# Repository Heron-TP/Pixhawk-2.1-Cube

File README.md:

# Pixhawk-2.1-Cube

This git repository contains a Carrier Board for the Pixhawk 2.1 Cube, using the open source EDA KiCad.
All hardware and coresponding EDA-files are subject to the CC-BY-SA 3.0 license.

All included or imported content is subject to its resprective licencing.

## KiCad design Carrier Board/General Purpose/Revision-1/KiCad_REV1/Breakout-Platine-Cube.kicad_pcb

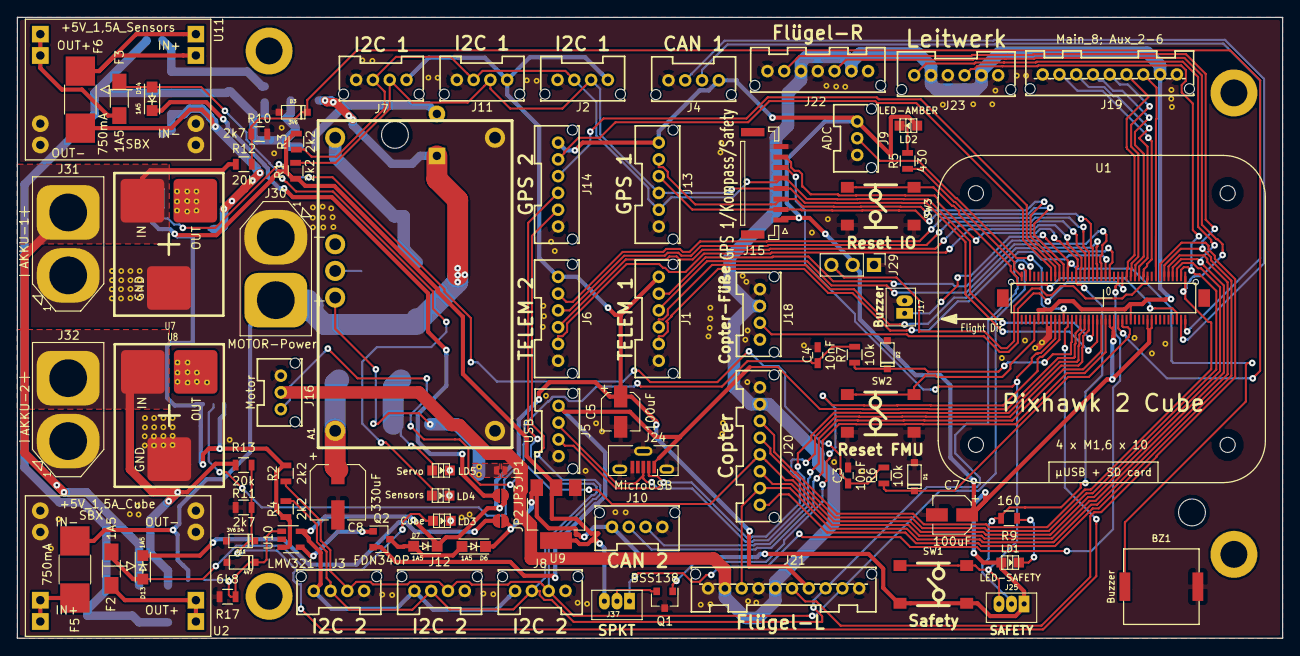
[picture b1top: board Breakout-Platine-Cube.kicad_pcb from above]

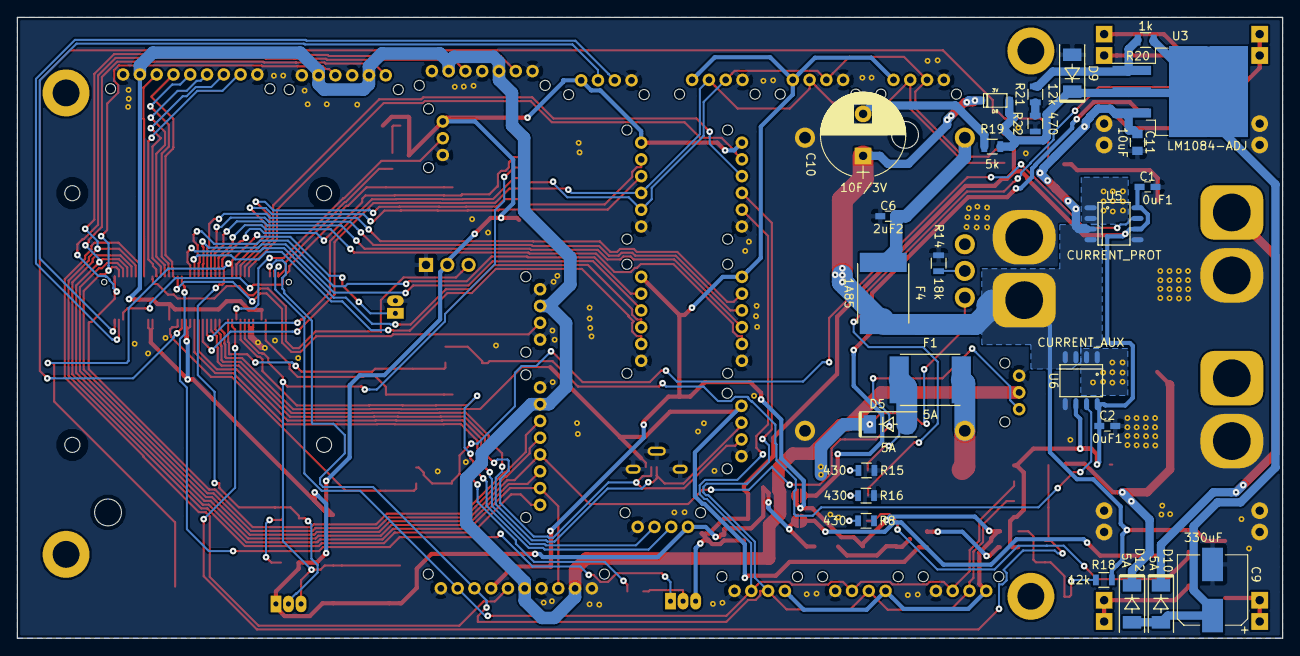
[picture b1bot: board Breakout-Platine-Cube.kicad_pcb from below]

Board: 2 copper layers, 150.8 x 74.0 mm, 108 parts (25 on the bottom side), 89 nets.

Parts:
A1: +5V_5A_Servo; TEXAS-R-PDSS-T7
BZ1: Buzzer; PKMCS0909E4000-R1
C1, C2: 0uF1; C_0603_HandSoldering
C3, C4: 10nF; C_0603_HandSoldering
C5, C7: 100uF; CP_Elec_4x5.8
C6: 2uF2; C_0603_HandSoldering
C8: 330uF; CP_Elec_6.3x5.8
C9: 330uF; CP_Elec_8x10.5
C10: 10F/3V; CP_Radial_D10.0mm_P5.00mm
C11: 10uF; C_0805
D1, D2, D3, D4: 3V6; sod123
D5, D10, D12: 5A; SOD-128
D6, D7, D13, D14: 1A5; SOD-123F
D8: 3V; sod123
D9: 30V/2W; SOD-128
D11: 4V7; sod123
F1: 5A; Fuse_SMD2920
F2, F3: 1A5; R_1206_HandSoldering
F4: 1A85; Fuse_SMD2920
F5, F6: 750mA; R_1812_HandSoldering
J1: TELEM 1; JST-PA-06_Top-entry-type
J2, J7, J11: I2C 1; JST-PA-04_Top-entry-type
J3, J8, J12: I2C 2; JST-PA-04_Top-entry-type
J4: CAN 1; JST-PA-04_Top-entry-type
J5: USB; JST-PA-04_Top-entry-type
J6: TELEM 2; JST-PA-06_Top-entry-type
J9: ADC; JST-PA-03_Top-entry-type
J10: CAN 2; JST-PA-04_Top-entry-type
J13: GPS 1; JST-PA-06_Top-entry-type
J14: GPS 2; JST-PA-06_Top-entry-type
J15: GPS 1/Kompass/Safety; JST_GH_BM08B-GHS-TBT_08x1.25mm_Straight
J16: Motor; JST-PA-03_Top-entry-type
J17: Buzzer; JST_ZH_B2B-ZR
J18: Copter-Füße; JST-PA-04_Top-entry-type
J19: Main_8; Aux_2-6; JST-PA-09_Top-entry-type
J20: Copter; JST-PA-08_Top-entry-type
J21: Flügel-L; JST-PA-10_Top-entry-type
J22: Flügel-R; JST-PA-07_Top-entry-type
J23: Leitwerk; JST-PA-06_Top-entry-type
J24: MicroUSB; USB_Micro-B_Vertical_Molex-105133-0001
J25: SAFETY; JST_ZH_B3B-ZR
J29: RC IN; Pin_Header_Straight_1x03_Pitch2.54mm
J30: MOTOR-Power; XT60-Top_Entry
J31: AKKU-1; XT60-Top_Entry
J32: AKKU-2; XT60-Top_Entry
J37: SPKT; JST_ZH_B3B-ZR
JP1: Servo; JUMPER-SOLDER-SMD_mit_flaechenanschluss
JP2: Cube; JUMPER-SOLDER-SMD
JP3: Sensors; JUMPER-SOLDER-SMD
LD1: LED-SAFETY; Led_0805
LD2: LED-AMBER; Led_0805
LD3: Cube; Led_0805
LD4: Sensors; Led_0805
LD5: Servo; Led_0805
Q1: BSS138; SOT-23
Q2: FDN340P; SOT-23
R1, R2, R3, R4: 2k2; R_0805
R5, R8, R15, R16: 430; R_0805
R6, R7: 10k; R_0805
R9: 160; R_0805
R10, R11: 2k7; R_0805
R12, R13: 20k; R_0805
R14: 18k; R_0805
R17: 6k8; R_0805
R18, R21: 12k; R_0805
R19: 5k; R_0805
R20: 1k; R_0805
R22: 470; R_0805
SW1: Safety; CK-PTS645-SMD
SW2: Reset FMU; CK-PTS645-SMD
SW3: Reset IO; CK-PTS645-SMD
U1: Pixhawk_2_Cube_80-Pin_Header; Pixhawk-2_Cube
U2: +5V_1,5A_Cube; Mini_MP1584EN
U3: LM1084-ADJ; TO-263-3_TabPin2
U5: CURRENT_PROT; SO-8
U6: CURRENT_AUX; SO-8
U7: Ideal_Diode_PROT; Ideale_Diode_Gen-I
U8: Ideal_Diode_AUX; Ideale_Diode_Gen-I
U9: LD1117S33TR_SOT223; SOT-223-3Lead_TabPin2
U10: LMV321; SOT-23-5
U11: +5V_1,5A_Sensors; Mini_MP1584EN

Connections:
+3V3: C1.1, C2.1, J37.3, R1.1, R2.1, R3.1, R4.1, U5.6, U5.8, U6.6, U6.8, U9.2, U10.3
+5V_Cube: C7.1, D6.2, J4.1, J9.1, J10.1, J13.1, J14.1, J15.1, J25.1, J29.2, JP2.1, LD1.1, LD2.1, SW1.1, SW1.2, U1.43, U1.45, U1.61, U1.63, U9.3
+5V_Sensors: C5.1, D7.2, J1.1, J2.1, J3.1, J6.1, J7.1, J8.1, J11.1, J12.1, J21.7, JP3.1, U10.5
+5V_Servo: J16.2, J18.2, J19.2, J20.2, J21.2, J21.5, J22.2, J22.5, J23.2, J23.5, JP1.1, U1.9, U1.53
/ALARM: BZ1.1, J17.1, U1.24
/AUX_BATT­_CURRENT_SENS: D2.2, R7.2, U1.25
/AUX_BATT­_CURRENT_SENS_1: C4.1, R7.1, U6.7
/AUX_BATT­_VOLTAGE_SENS: D4.2, R11.1, R13.2, U1.23
/BATT­_CURRENT_SENS_PROT: D1.2, R6.2, U1.49
/BATT­_CURRENT_SENS_PROT_1: C3.1, R6.1, U5.7
/BATT­_VOLTAGE_SENS_PROT: D3.2, R10.1, R12.2, U1.47
/CAN_H_1: J4.2, U1.79
/CAN_H_2: J10.2, U1.41
/CAN_L_1: J4.3, U1.77
/CAN_L_2: J10.3, U1.39
/FMU-CH1-PROT: J18.3, U1.50
/FMU-CH2-PROT: J19.4, U1.52
/FMU-CH3-PROT: J19.5, U1.54
/FMU-CH4-PROT: J19.6, U1.56
/FMU-CH5-PROT: J19.7, U1.58
/FMU-CH6-PROT: J19.8, U1.60
/FMU-~LED_AMBER: R5.1, U1.2
/FMU-~RESET: SW2.1, SW2.2, U1.7
/I2C_1_SCL: J2.2, J7.2, J11.2, J13.4, J15.4, R1.2, U1.37
/I2C_1_SDA: J2.3, J7.3, J11.3, J13.5, J15.5, R3.2, U1.35
/I2C_2_SCL: J3.2, J8.2, J12.2, J14.4, J21.8, R4.2, U1.6
/I2C_2_SDA: J3.3, J8.3, J12.3, J14.5, J21.9, R2.2, U1.4
/IO-CH1-PROT: J20.3, J22.3, U1.80
/IO-CH2-PROT: J20.4, J23.3, U1.78
/IO-CH3-PROT: J16.3, J20.5, U1.76
/IO-CH4-PROT: J20.6, J23.6, U1.74
/IO-CH5-PROT: J20.7, J21.3, U1.72
/IO-CH6-PROT: J20.8, J22.6, U1.70
/IO-CH7-PROT: J21.6, U1.68
/IO-CH8-PROT: J19.3, U1.66
/IO-USART1_RX_SPECTRUM_DSM: J37.1, U1.48
/IO-~LED_SAFETY_PROT: J15.7, J25.2, R9.2, U1.28
/IO-~RESET: SW3.1, SW3.2, U1.75
/OTG_DM1: J5.3, J24.2, U1.33
/OTG_DP1: J5.2, J24.3, U1.31
/PPM_SBUS_PROT: J29.3, U1.62
/PREASSURE_SENS_IN: J9.2, U1.21
/Power_Supply/Power_Supply: C10.1, C11.1, D8.2, F4.1, F5.1, F6.1, J30.1, R18.1, U3.3, U5.3, U5.4, U6.3, U6.4
/Power_Supply/Recuperate: C9.1, D8.1, D9.2, D10.1, D12.1, R19.2, R20.1, U3.2
/SAFETY: J15.6, J25.3, SW1.3, SW1.4, U1.17
/SERIAL1_CTS: J1.4, U1.44
/SERIAL1_RTS: J1.5, U1.42
/SERIAL1_RX: J1.3, U1.38
/SERIAL1_TX: J1.2, U1.40
/SERIAL2_CTS: J6.4, U1.32
/SERIAL2_RTS: J6.5, U1.30
/SERIAL2_RX: J6.3, U1.34
/SERIAL2_TX: J6.2, U1.36
/SERIAL_3_RX: J13.2, J15.3, U1.20
/SERIAL_3_TX: J13.3, J15.2, U1.22
/SERIAL_4_RX: J14.2, U1.16
/SERIAL_4_TX: J14.3, U1.18
/VBUS: J5.1, J24.1, Q2.2, U1.29
/VDD_3V3_SPECTRUM_EN: Q1.1, U1.19
GND: A1.1, A1.7, BZ1.2, C1.2, C2.2, C3.2, C4.2, C5.2, C6.1, C7.2, C8.2, C9.2, C11.2, D1.1, D2.1, D3.1, D4.1, D9.1, D11.1, J1.6, J2.4, J3.4, J4.4, J5.4, J6.6, J7.4, J8.4, J9.3, J10.4, J11.4, J12.4, J13.6, J14.6, J15.8, J16.1, J17.2, J18.1, J18.4, J19.1, J19.9, J20.1, J21.1, J21.4, J21.10, J22.1, J22.4, J22.7, J23.1, J23.4, J24.5, J24.6, J29.1, J30.2, J31.2, J32.2, Q1.3, R8.1, R10.2, R11.2, R14.1, R15.1, R16.1, R17.2, R22.1, SW2.3, SW2.4, SW3.3, SW3.4, U1.13, U1.15, U2.3, U2.4, U2.5, U2.6, U5.5, U6.5, U7.3, U8.3, U9.1, U10.2, U11.3, U11.4, U11.5, U11.6
unnamed: A1.2, C6.2, F4.2
unnamed: A1.4, R14.2
unnamed: A1.5, D5.2, JP1.2
unnamed: A1.6, C8.1, F1.1
unnamed: C10.2, R19.1
unnamed: D5.1, F1.2, LD5.1
unnamed: D6.1, D7.1, Q2.3
unnamed: D10.2, J31.1, R12.1, U7.1
unnamed: D11.2, R17.1, R18.2, U10.1
unnamed: D12.2, J32.1, R13.1, U8.1
unnamed: D13.1, F2.2, LD3.1
unnamed: D13.2, JP2.2
unnamed: D14.1, F3.2, LD4.1
unnamed: D14.2, JP3.2
unnamed: F2.1, U2.7, U2.8
unnamed: F3.1, U11.7, U11.8
unnamed: F5.2, U2.1, U2.2
unnamed: F6.2, U11.1, U11.2
unnamed: J37.2, Q1.2
unnamed: LD1.2, R9.1
unnamed: LD2.2, R5.2
unnamed: LD3.2, R8.2
unnamed: LD4.2, R16.2
unnamed: LD5.2, R15.2
unnamed: Q2.1, U10.4
unnamed: R20.2, R21.2, U3.1
unnamed: R21.1, R22.2
unnamed: U5.1, U5.2, U7.2
unnamed: U6.1, U6.2, U8.2

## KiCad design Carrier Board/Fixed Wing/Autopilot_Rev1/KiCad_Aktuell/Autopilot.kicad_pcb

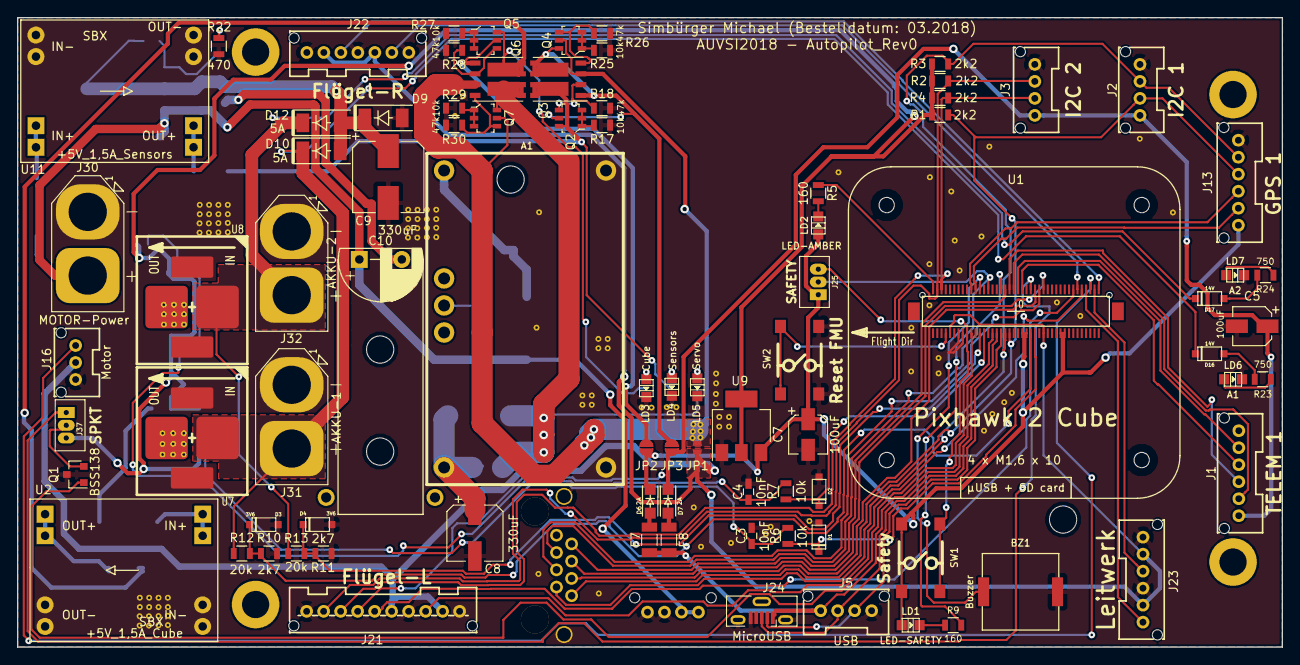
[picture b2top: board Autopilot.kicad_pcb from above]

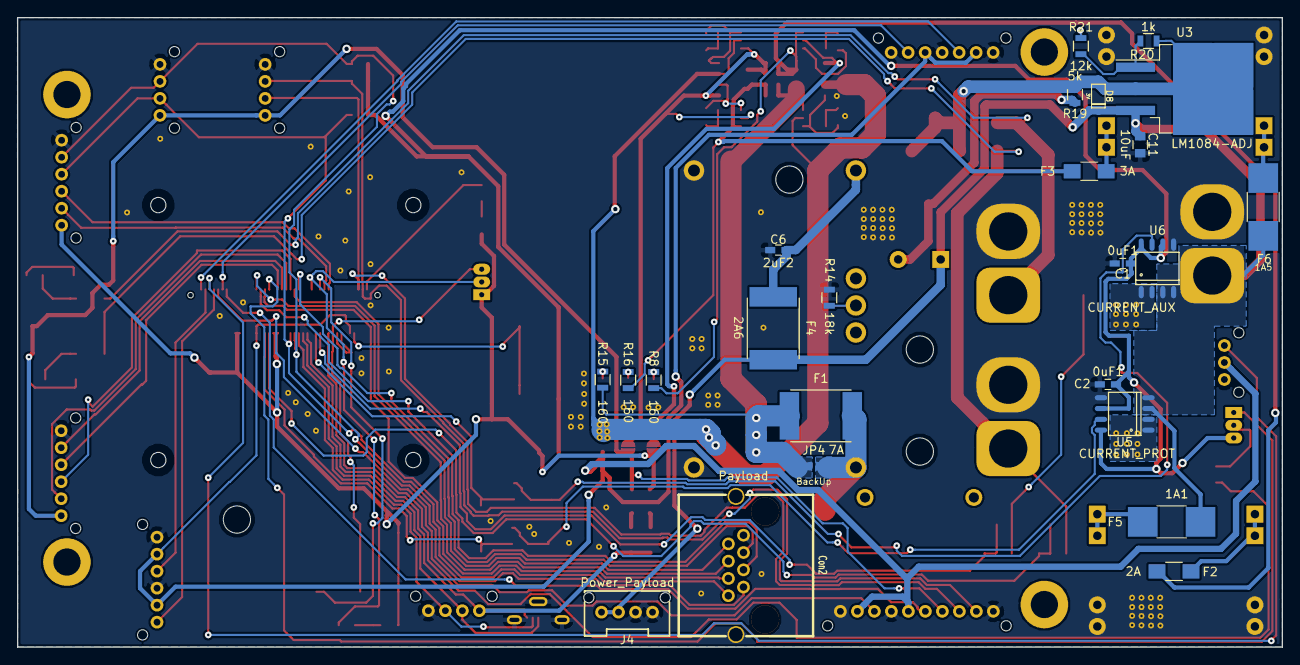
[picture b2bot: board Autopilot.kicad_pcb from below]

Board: 2 copper layers, 148.8 x 74.1 mm, 109 parts (24 on the bottom side), 85 nets.

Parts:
A1: +5V3_6A_Servo; TEXAS-R-PDSS-T7
BZ1: Buzzer; PKMCS0909E4000-R1
C1, C2: 0uF1; C_0603_HandSoldering
C3, C4: 10nF; C_0603_HandSoldering
C5, C7: 100uF; CP_Elec_4x5.8
C6: 2uF2; C_0603_HandSoldering
C8: 330uF; CP_Elec_6.3x5.8
C9: 330uF; CP_Elec_8x10.5
C10: 10F/3V; CP_Radial_D10.0mm_P5.00mm_horizontal
C11: 10uF; C_0805
Con2: Payload; RJHSE-5380
D1, D2, D3, D4: 3V6; sod123
D6, D7: 2A; SOD-123F
D8: 3V; sod123
D9: 30V/2W; SOD-128
D10, D12: 5A; SOD-128
D16, D17: 14V; sod123
F1: 7A; Fuse_SMD2920
F2: 2A; R_1206_HandSoldering
F3: 3A; R_1206_HandSoldering
F4: 2A6; Fuse_SMD2920
F5: 1A1; R_1812_HandSoldering
F6: 1A5; R_1812_HandSoldering
F7, F8: 1A5; R_1206_3216Metric
J1: TELEM 1; JST-PA-06_Top-entry-type
J2: I2C 1; JST-PA-04_Top-entry-type
J3: I2C 2; JST-PA-04_Top-entry-type
J4: Power_Payload; JST-PA-04_Top-entry-type
J5: USB; JST-PA-04_Top-entry-type
J13: GPS 1; JST-PA-06_Top-entry-type
J16: Motor; JST-PA-03_Top-entry-type
J21: Flügel-L; JST-PA-10_Top-entry-type
J22: Flügel-R; JST-PA-07_Top-entry-type
J23: Leitwerk; JST-PA-06_Top-entry-type
J24: MicroUSB; USB_Micro-B_Vertical_Molex-105133-0001
J25: SAFETY; JST_ZH_B3B-ZR
J30: MOTOR-Power; XT60-Top_Entry
J31: AKKU-1; XT60-Top_Entry
J32: AKKU-2; XT60-Top_Entry
J37: SPKT; JST_ZH_B3B-ZR
JP1: Servo; JUMPER-SOLDER-SMD_mit_flaechenanschluss
JP2: Cube; JUMPER-SOLDER-SMD
JP3: Sensors; JUMPER-SOLDER-SMD
JP4: BackUp; JUMPER-SOLDER-SMD_mit_flaechenanschluss
LD1: LED-SAFETY; Led_0805
LD2: LED-AMBER; Led_0805
LD3: Cube; Led_0805
LD4: Sensors; Led_0805
LD5: Servo; Led_0805
LD6: A1; Led_0805
LD7: A2; Led_0805
Q1: BSS138; SOT-23
Q2, Q4, Q5, Q7: DMMT5401-7-F; SOT-23-6
Q3, Q6: SI7997DP; PowerPAK_SO-8_Dual
R1, R2, R3, R4: 2k2; R_0805
R5, R8, R9, R15, R16: 160; R_0805
R6, R7, R17, R25, R27, R29: 10k; R_0805
R10, R11: 2k7; R_0805
R12, R13: 20k; R_0805
R14: 18k; R_0805
R18, R26, R28, R30: 47k; R_0805
R19: 5k; R_0805
R20: 1k; R_0805
R21: 12k; R_0805
R22: 470; R_0805
R23, R24: 750; R_0805
SW1: Safety; CK-PTS645-SMD
SW2: Reset FMU; CK-PTS645-SMD
U1: Pixhawk_2_Cube_80-Pin_Header; Pixhawk-2_Cube
U2: +5V_1,5A_Cube; Mini_MP1584EN
U3: LM1084-ADJ; TO-263-3_TabPin2
U5: CURRENT_PROT; SO-8
U6: CURRENT_AUX; SO-8
U7: Ideal_Diode_PROT; Ideale_Diode_Gen-II_rev00
U8: Ideal_Diode_AUX; Ideale_Diode_Gen-II_rev00
U9: LD1117S33TR_SOT223; SOT-223-3Lead_TabPin2
U11: +5V_1,5A_Sensors; Mini_MP1584EN

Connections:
+3V3: C1.1, C2.1, J37.3, R1.1, R2.1, R3.1, R4.1, U5.6, U5.8, U6.6, U6.8, U9.2
+5V_Cube: C7.1, D6.2, J13.1, J25.1, JP2.1, LD1.1, LD2.1, SW1.1, SW1.2, U1.43, U1.45, U1.61, U1.63, U9.3
+5V_Sensors: C5.1, D7.2, J1.1, J2.1, J3.1, J21.7, JP3.1
+5V_Servo: J16.2, J21.2, J21.5, J22.2, J22.5, J23.2, J23.5, JP1.1, U1.9, U1.53
/ALARM: BZ1.1, U1.24
/AUX_BATT­_CURRENT_SENS: D2.2, R7.2, U1.25
/AUX_BATT­_CURRENT_SENS_1: C4.1, R7.1, U6.7
/AUX_BATT­_VOLTAGE_SENS: D4.2, R11.1, R13.2, U1.23
/BATT­_CURRENT_SENS_PROT: D1.2, R6.2, U1.49
/BATT­_CURRENT_SENS_PROT_1: C3.1, R6.1, U5.7
/BATT­_VOLTAGE_SENS_PROT: D3.2, R10.1, R12.2, U1.47
/FMU-CH1-PROT: Con2.6, U1.50
/FMU-CH2-PROT: Con2.5, U1.52
/FMU-CH3-PROT: Con2.4, U1.54
/FMU-~LED_AMBER: R5.1, U1.2
/FMU-~RESET: SW2.1, SW2.2, U1.7
/I2C_1_SCL: Con2.8, J2.2, J13.4, R1.2, U1.37
/I2C_1_SDA: Con2.7, J2.3, J13.5, R3.2, U1.35
/I2C_2_SCL: J3.2, J21.8, R4.2, U1.6
/I2C_2_SDA: J3.3, J21.9, R2.2, U1.4
/IO-CH1-PROT: J22.3, U1.80
/IO-CH2-PROT: J23.3, U1.78
/IO-CH3-PROT: J16.3, U1.76
/IO-CH4-PROT: J23.6, U1.74
/IO-CH5-PROT: J21.3, U1.72
/IO-CH6-PROT: J22.6, U1.70
/IO-CH7-PROT: J21.6, U1.68
/IO-USART1_RX_SPECTRUM_DSM: J37.1, U1.48
/IO-~LED_SAFETY_PROT: J25.2, R9.2, U1.28
/OTG_DM1: J5.3, J24.2, U1.33
/OTG_DP1: J5.2, J24.3, U1.31
/Power_Supply: C10.1, C11.1, D8.2, F4.1, F5.1, F6.1, J4.1, J4.2, J30.1, U3.3, U5.3, U5.4, U6.3, U6.4
/Power_Supply/CrossFeed: JP1.2, Q3.3, Q4.5, Q6.3, Q7.5
/Power_Supply/ID_CrossFeed: JP3.2, Q2.5, Q3.1, Q3.6, Q4.6
/Power_Supply/ID_Cub_1: F2.2, Q5.6, Q6.5, R8.2
/Power_Supply/ID_Cub_2: JP2.2, Q5.5, Q6.1
/Power_Supply/ID_Sen_1: F3.2, Q2.6, Q3.5, R16.2
/Power_Supply/ID_Ser_1: F1.2, JP4.1, Q6.6, Q7.6, R15.2
/Power_Supply/Recuperate: C9.1, D8.1, D9.2, D10.1, D12.1, R19.2, R20.1, U3.2
/SAFETY: J25.3, SW1.3, SW1.4, U1.17
/SERIAL1_CTS: J1.4, U1.44
/SERIAL1_RTS: J1.5, U1.42
/SERIAL1_RX: J1.3, U1.38
/SERIAL1_TX: J1.2, U1.40
/SERIAL2_RX: Con2.3, U1.34
/SERIAL2_TX: Con2.2, U1.36
/SERIAL_3_RX: J13.3, U1.20
/SERIAL_3_TX: J13.2, U1.22
/VBUS: F7.1, F8.1, J5.1, J24.1, U1.29
/VDD_3V3_SPECTRUM_EN: Q1.1, U1.19
GND: A1.1, A1.7, BZ1.2, C1.2, C2.2, C3.2, C4.2, C5.2, C6.1, C7.2, C8.2, C9.2, C11.2, Con2.1, Con2.9, D1.1, D2.1, D3.1, D4.1, D9.1, J1.6, J2.4, J3.4, J4.3, J4.4, J5.4, J13.6, J16.1, J21.1, J21.4, J21.10, J22.1, J22.4, J22.7, J23.1, J23.4, J24.5, J24.6, J30.2, J31.2, J32.2, LD3.2, LD4.2, LD5.2, LD6.2, LD7.2, Q1.3, R10.2, R11.2, R14.1, R17.1, R18.1, R22.1, R25.1, R26.1, R27.1, R28.1, R29.1, R30.1, SW2.3, SW2.4, U1.13, U1.15, U2.3, U2.4, U2.5, U2.6, U5.5, U6.5, U7.3, U8.3, U9.1, U11.3, U11.4, U11.5, U11.6
unnamed: A1.2, C6.2, F4.2
unnamed: A1.4, R14.2
unnamed: A1.6, C8.1, F1.1, JP4.2
unnamed: C10.2, R19.1
unnamed: D6.1, F7.2
unnamed: D7.1, F8.2
unnamed: D10.2, D16.2, J31.1, R12.1, U7.1
unnamed: D12.2, D17.2, J32.1, R13.1, U8.1
unnamed: D16.1, R23.2
unnamed: D17.1, R24.2
unnamed: F2.1, U2.7, U2.8
unnamed: F3.1, U11.7, U11.8
unnamed: F5.2, U2.1, U2.2
unnamed: F6.2, U11.1, U11.2
unnamed: J37.2, Q1.2
unnamed: LD1.2, R9.1
unnamed: LD2.2, R5.2
unnamed: LD3.1, R8.1
unnamed: LD4.1, R16.1
unnamed: LD5.1, R15.1
unnamed: LD6.1, R23.1
unnamed: LD7.1, R24.1
unnamed: Q2.1, Q2.2, Q2.3, R17.2
unnamed: Q2.4, Q3.2, R18.2
unnamed: Q3.4, Q4.4, R26.2
unnamed: Q4.1, Q4.2, Q4.3, R25.2
unnamed: Q5.1, Q5.2, Q5.3, R27.2
unnamed: Q5.4, Q6.2, R28.2
unnamed: Q6.4, Q7.4, R30.2
unnamed: Q7.1, Q7.2, Q7.3, R29.2
unnamed: R20.2, R21.2, U3.1
unnamed: R21.1, R22.2
unnamed: U5.1, U5.2, U7.2
unnamed: U6.1, U6.2, U8.2

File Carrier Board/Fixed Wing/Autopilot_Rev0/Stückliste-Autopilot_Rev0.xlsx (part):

Reference | Value | Footprint | Count | Datasheet | FootprintLib | banggood# | digikey# | farnell# | manf# | vorhanden | #mouser | Manufacturer | mouser# | bangood# | BOM
U1 | Pixhawk_2_Cube_80-Pin_Header | Pixhawk-2_Cube | 1 |  | Pixhawk_2-Cube | Value | Value | 1874484 | DF17(1.0H)-80DP-0.5V(57) | Value
J2 | I2C 1 | JST-PA-04_Top-entry-type | 1 |  | JST_PA
R1;R3;R2;R4 | 2k2 | R_0805 | 4 |  | Resistors-Mini-SMD |  |  |  | vorhanden [0805]
J3 | I2C 2 | JST-PA-04_Top-entry-type | 1 |  | JST_PA
J1 | TELEM 1 | JST-PA-06_Top-entry-type | 1 |  | JST_PA
J13 | GPS 1 | JST-PA-06_Top-entry-type | 1 |  | JST_PA |  |  |  | B06B-PASK-1 [vorhanden]
J5 | USB | JST-PA-04_Top-entry-type | 1 |  | JST_PA
J23 | Leitwerk | JST-PA-06_Top-entry-type | 1 |  | JST_PA |  | Value |  | B06B-PASK-1(LF)(SN) | ja
J16 | Motor | JST-PA-03_Top-entry-type | 1 |  | JST_PA |  | 455-1833-ND |  | B03B-PASK-1(LF)(SN) | ja
J21 | Flügel-L | JST-PA-10_Top-entry-type | 1 |  | JST_PA |  | Value |  | B10B-PASK-1(LF)(SN) | ja
J22 | Flügel-R | JST-PA-07_Top-entry-type | 1 |  | JST_PA |  | 455-1837-ND |  | B07B-PASK-1(LF)(SN)
R5;R9;R16;R8;R15 | 160 | R_0805 | 5 |  | Resistors-Mini-SMD |  |  |  | vorhanden [0805]
SW2 | Reset FMU | CK-PTS645-SMD | 1 |  | manuf |  | CKN9112CT-ND |  | PTS645SM43SMTR92 LFS | Value
J24 | MicroUSB | USB_Micro-B_Vertical_Molex-105133-0001 | 1 |  | Connectors_USB |  | WM9734CT-ND |  | 1051330001 | Value
BZ1 | Buzzer | PKMCS0909E4000-R1 | 1 |  | devices_[JS] | Value | 490-9647-1-ND | Value | PKMCS0909E4000-R1 | - | -
SW1 | Safety | CK-PTS645-SMD | 1 |  | manuf |  | CKN9084CT-ND |  | PTS645SK43SMTR92 LFS | Value
J25 | SAFETY | JST_ZH_B3B-ZR | 1 |  | JST_ZH |  | 455-1658-ND |  | B3B-ZR(LF)(SN) | Value
R6;R7;R17;R25;R27;R29 | 10k | R_0805 | 6 |  | Resistors-Mini-SMD |  |  |  | vorhanden [0805]
J37 | SPKT | JST_ZH_B3B-ZR | 1 |  | JST_ZH |  | 455-1658-ND |  | B3B-ZR(LF)(SN) | Value
LD2 | LED-AMBER | Led_0805 | 1 |  | w_smd_leds | Value | 160-1413-1-ND | Value | LTST-C170KFKT | Value
LD1 | LED-SAFETY | Led_0805 | 1 |  | w_smd_leds | Value | CMDA5DR7D1SCT-ND | Value | CMDA5DR7D1SCT-ND | Value
D2;D1;D3;D4 | 3V6 | sod123 | 4 |  | w_smd_diode | Value | MMSZ4685-TPMSCT-ND | Value | MMSZ4685-TP | Value
Q1 | BSS138 | SOT-23 | 1 |  | TO_SOT_Packages_SMD | Value | BSS138CT-ND | 9845330 | BSS138 | Value | -
C7;C5 | 100uF | CP_Elec_4x5.8 | 2 |  | Capacitors_SMD | Value | P15076CT-ND | Value | EEE-FT0J101AR | Value
Con2 | Payload | RJHSE-5380 | 1 | https://www.amphenolcanada.com/ProductSearch/drawings/AC/RJH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 | conn-ethernet-[JS]
J4 | Power_Payload | JST-PA-04_Top-entry-type | 1 |  | JST_PA
R12;R13 | 20k | R_0805 | 2 |  | Resistors-Mini-SMD |  |  |  | vorhanden [0805]
R10;R11 | 2k7 | R_0805 | 2 |  | Resistors-Mini-SMD |  |  |  | vorhanden [0805]
F5 | 1A1 | R_1812_HandSoldering | 1 |  | Resistors_SMD | Value | 507-1768-1-ND | Value | 0ZCG0110BF2B | Value
J31 | AKKU-1 | XT60-Top_Entry | 1 |  | UAV-Modules-[JS] |  |  |  | vorhanden
J32 | AKKU-2 | XT60-Top_Entry | 1 |  | UAV-Modules-[JS] |  |  |  | vorhanden
J30 | MOTOR-Power | XT60-Top_Entry | 1 |  | UAV-Modules-[JS] |  |  |  | vorhanden
U6 | CURRENT_AUX | SO-8 | 1 | http://www.allegromicro.com/~/media/Files/Datasheets/ACS722-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 | Power_Integrations |  | 620-1640-1-ND |  | ACS722LLCTR-40AU-T | Value |  | Allegro Microsystems
C2;C1 | 0uF1 | C_0603_HandSoldering | 2 |  | Capacitors_SMD |  | 399-5089-1-ND |  | C0603C104K5RACTU | Value
C4;C3 | 10nF | C_0603_HandSoldering | 2 |  | Capacitors_SMD |  | 399-1091-1-ND |  | C0603C103K5RACTU | Value
U5 | CURRENT_PROT | SO-8 | 1 | http://www.allegromicro.com/~/media/Files/Datasheets/ACS722-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 | Power_Integrations |  | 620-1640-1-ND |  | ACS722LLCTR-40AU-T | Value |  | Allegro Microsystems
F4 | 2A6 | Fuse_SMD2920 | 1 |  | con-lumberg | Value | MF-LSMF260X-2CT-ND | Value | MF-LSMF260X-2 | x
F2 | 2A | R_1206_HandSoldering | 2 | http://www.bourns.com/docs/Product-Datasheets/mfnsml.pdf | Resistors_SMD | Value | MF-NSML200-2CT-ND | Value | MF-NSML200-2 | Value |  |  | Value | Value
F1 | 7A | Fuse_SMD2920 | 1 | http://www.littelfuse.com/~/media/electronics/datasheets/res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 | con-lumberg | Value | F6137CT-ND | Value | 2920L700SLPR | Value | - |  | Value | Value
U8 | Ideal_Diode_AUX | Ideale_Diode_Gen-I | 1 |  | Ideale-Diode-pcb_[JS] |  |  |  | vorhanden
U7 | Ideal_Diode_PROT | Ideale_Diode_Gen-I | 1 |  | Ideale-Diode-pcb_[JS] |  |  |  | vorhanden
U9 | LD1117S33TR_SOT223 | SOT-223-3Lead_TabPin2 | 1 |  | TO_SOT_Packages_SMD | Value | 497-1242-1-ND | Value | LD1117S33TR | Value
LD4 | Sensors | Led_0805 | 1 |  | w_smd_leds | Value | 754-1127-1-ND | Value | APT2012CGCK | Value
LD3 | Cube | Led_0805 | 1 |  | w_smd_leds | Value | 754-1127-1-ND | Value | APT2012CGCK | Value
JP1 | Servo | JUMPER-SOLDER-SMD | 1 |  | conn-test
JP2 | Cube | JUMPER-SOLDER-SMD | 1 |  | conn-test
JP3 | Sensors | JUMPER-SOLDER-SMD | 1 |  | conn-test
A1 | +5V3_6A_Servo | TEXAS-R-PDSS-T7 | 1 | http://www.ti.com/lit/ds/symlink/ptn78020h.pdf | manuf | Value | 296-20515-ND | Value | PTN78020WAH | Value |  |  | Value | Value | ASSY TI PTN78000WAH
C6 | 2uF2 | C_0603_HandSoldering | 1 |  | Capacitors_SMD | Value | 1276-6726-1-ND | Value | CL10A225KL8NNNC | Value
R14 | 18k | R_0805 | 1 |  | Resistors-Mini-SMD | Value | 311-18.0KCRCT-ND | Value | RC0805FR-0718KL | Value | -
C8 | 330uF | CP_Elec_6.3x5.8 | 1 |  | Capacitors_SMD | Value | P15080CT-ND | Value | EEE-FT0J331AP | Value |  |  | Value | Value
LD5 | Servo | Led_0805 | 1 |  | w_smd_leds | Value | 754-1127-1-ND | Value | APT2012CGCK | Value
U2 | +5V_1,5A_Cube | Mini_MP1584EN | 1 | https://www.openimpulse.com/blog/wp-content/uploads/wpsc/dow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 | Power-IC | 951167 (1096121) | Value | Value | Value | Value | - |  | Value | Value
U11 | +5V_1,5A_Sensors | Mini_MP1584EN | 1 | https://www.openimpulse.com/blog/wp-content/uploads/wpsc/dow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 | Power-IC | 951167 (1096121) | Value | Value | Value | Value | - |  | Value | Value
D10;D12 | 5A | SOD-128 | 2 |  | General_smd-[JS] | Value | 1727-5207-1-ND | Value | PMEG3050BEP,115 | Value | -
U3 | LM1084-ADJ | TO-263-3_TabPin2 | 1 |  | TO_SOT_Packages_SMD | Value | LM1084IS-ADJ/NOPB-ND | 1469033 | LM1084IS-ADJ/NOPB | Value | 926-LM1084ISXADJNOPB
C11 | 10uF | C_0805 | 1 |  | Capacitors_SMD | Value | 490-10514-1-ND | 2528772 | GRM21BR6YA106KE43L | Value | -
D9 | 30V/2W | SOD-128 | 1 |  | General_smd-[JS] | Value | DZ2430000LCT-ND | Value | DZ2430000L | Value | -
C9 | 330uF | CP_Elec_8x10.5 | 1 |  | Capacitors_SMD | Value | PCE5118CT-ND | Value | EEE-FT1V331GP | P15080CT-ND | -
R20 | 1k | R_0805 | 1 |  | Resistors-Mini-SMD |  |  |  | vorhanden [0805]
R22 | 470 | R_0805 | 1 |  | Resistors-Mini-SMD |  |  |  | vorhanden [0805]
R21 | 12k | R_0805 | 1 |  | Resistors-Mini-SMD |  |  |  | vorhanden [0805]
C10 | 10F/3V | CP_Radial_D10.0mm_P5.00mm | 1 | http://datasheets.avx.com/AVX-SCC-3.0V.pdf | Capacitors_THT | Value | 478-11287-ND | Value | SCCS30E106SRB | Value | - |  | Value | Value
R19 | 5k | R_0805 | 1 |  | Resistors-Mini-SMD |  |  |  | vorhanden [0805]
D8 | 3V | sod123 | 1 |  | w_smd_diode | Value | DDZ9683-7DICT-ND | Value | DDZ9683-7 | Value | -
R24;R23 | 750 | R_0805 | 2 |  | Resistors-Mini-SMD |  |  |  | vorhanden [0805]
LD6;LD7 | A2 | Led_0805 | 2 | http://katalog.we-online.de/led/datasheet/150080BS75000.pdf | w_smd_leds | Value | 732-4982-1-ND | Value | 150080BS75000 | Value |  |  | Value | Value
D17;D16 | 14V | sod123 | 2 |  | w_smd_diode | Value | MMSZ4701-TPMSCT-ND | Value | MMSZ4701-TP | Value
D6;D7 | 2A | SOD-123F | 2 |  | General_smd-[JS] | Value | 1727-3873-1-ND | Value | PMEG3020EH,115 | Value | -
F8;F7 | 1A5 | R_1206_3216Metric | 2 |  | Resistor_SMD | Value | F3372CT-ND | Value | 1206L150THWR | Value
R18;R26;R28;R30 | 47k | R_0805 | 4 |  | Resistors-Mini-SMD |  |  |  | vorhanden [0805]
Q2;Q4;Q5;Q7 | DMMT5401-7-F | SOT-23-6 | 4 | https://www.diodes.com/assets/Datasheets/ds30437.pdf | digikey-footprints |  | Value | Value | Value | - |  |  | Value | Value
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
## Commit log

2018-09-22 Create Breakout-Platine-Cube
2018-09-28 Create Entwicklungsdokumentation
    creating folder sturktur
2018-09-28 Delete Entwicklungsdokumentation
    test
2018-09-28 -initial commit
2018-09-28 Create License
    license note
2018-09-28 Create CC BY-SA 3.0 GER
    CC BY-SA 3.0 GER
2018-09-28 Create License-ENG
    just in case, English version
